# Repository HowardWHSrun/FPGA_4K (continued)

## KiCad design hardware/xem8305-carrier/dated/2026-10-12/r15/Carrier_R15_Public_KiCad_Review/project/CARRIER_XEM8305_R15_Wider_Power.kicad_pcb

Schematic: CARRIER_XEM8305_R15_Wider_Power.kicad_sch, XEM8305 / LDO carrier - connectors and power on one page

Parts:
C5: 220 uF / 25 V; EEE_FK1E221P; MPN EEE-FK1E221P
C6, C38, C48: 0.1 uF / 25 V; C_0402; MPN TMK105BJ104KV-F
C34, C53: 0.1 uF / 10 V; C_0402; MPN C0402C104K8PACTU
C47: 22 uF / 35 V; C_1206; MPN C3216X5R1V226M160AC
C49, C50: 22 uF / 10 V; C_1206; MPN LMK316AB7226KL-TR
C54: 10 pF / 50 V; C_0402; MPN CBR04C100J5GAC
C55: 3.3 nF / 50 V; C_0402; MPN C0402C332K5RACTU
C56: 1 uF / 10 V; C_0402; MPN LMK105BJ105KV-F
C500, C501, C505, C511, C513: 4.7uF; C_0402_1005Metric; MPN JMK105BBJ475MV-F
C502, C503, C504, C506, C507, C508, C509, C512, C514, C515, C516, C517, C518, C519, C520, C522, C525, C526, C527, C528: 100nF; C_0402_1005Metric; MPN C0402C104K8PACTU
C510, C521: 10nF; C_0402_1005Metric; MPN C0402C103K4RACTU
C523, C524: 18pF; C_0402_1005Metric; MPN C0402C180J5GACTU
D4: SMBJ15CA-13-F; D_SMB; MPN SMBJ15CA-13-F
D500: D5V0FS4U10LP-7; Diodes_UDFN-10_1x2.5mm_P0.5mm; MPN D5V0FS4U10LP-7
FB500, FB501, FB502: 600R @100MHz; L_0603_1608Metric; MPN MI0603J601R-10
FB503: 220R @100MHz; L_0805_2012Metric; MPN BLM21PG221SN1D
J1: DF40C(2.0)-50DS-0.4V(51); Hirose_DF40C(2.0)-50DS-0.4V_2x25_P0.4mm; MPN DF40C(2.0)-50DS-0.4V(51)
J4: PJ-102AH; PJ102AH; MPN PJ-102AH
J19: DF40C(2.0)-24DS-0.4V(51); Hirose_DF40C(2.0)-24DS-0.4V_2x12_P0.4mm; MPN DF40C(2.0)-24DS-0.4V(51)
J500: USB4110-GF-A; USB_C_Receptacle_GCT_USB4110; MPN USB4110-GF-A
JP1: REMOVE FOR EXT 3V3; PinHeader_1x02_P2_54; MPN TBD - 2-pin 2.54 mm vertical header plu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
L14: 3.3 uH; Murata_1267AY; MPN 1267AY-3R3N=P3
MC1: ERF6-50-03.5-L-DV-A-K-TR; MPN ERF6-50-03.5-L-DV-A-K-TR
MC2, MC3: ERF6-40-03.5-L-DV-A-K-TR; MPN ERF6-40-03.5-L-DV-A-K-TR
MH1, MH2, MH3, MH4: M3 isolated; MountingHole_3.2mm_M3_Isolated
R75: 10.0 k / 1%; R_0402; MPN CRCW040210K0FKED
R77: 73.2 k / 1%; R_0402; MPN CRCW040273K2FKED
R78: 22.1 k / 1%; R_0402; MPN CRCW040222K1FKEDC
R500, R501: 5.1k; R_0402_1005Metric; MPN CRCW04025K10FKEDC
R502: 12k; R_0402_1005Metric; MPN CRCW040212K0FKED
R503, R510: 10k; R_0402_1005Metric; MPN CRCW040210K0FKED
R507, R508: 100k; R_0402_1005Metric; MPN CRCW0402100KFKED
R509: 2k; R_0402_1005Metric; MPN CRCW04022K00FKED
TP19: 3V3 TEST / EXT+; TestPoint_PTH_D1_Pad2_5
TP20: GND / EXT-; TestPoint_PTH_D1_Pad2_5
U10: TPS54429E; TPS54429E_RSA; MPN TPS54429ERSAR
U500, U502, U503, U504: SN74AXC1T45DBVR; SOT-23-6; MPN SN74AXC1T45DBVR
U501: FT232HQ; QFN-48-1EP_8x8mm_P0.5mm_EP6.2x6.2mm; MPN FT232HQ
U505: 93LC56B-E/MS; MSOP-8_3x3mm_P0.65mm; MPN 93LC56B-E/MS
Y500: 12MHz / 18pF; Crystal_SMD_3225-4Pin_3.2x2.5mm; MPN ABM8-12.000MHZ-B2-T

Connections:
/CHIP_RESET: J1.14 (CHIP_RESET), MC1.85 (B64_L7N)
/CLK32MHZ: J1.36 (CLK32MHZ), MC1.67 (B64_L11P_GC)
/CLKH: J1.12 (CLKH), MC1.78 (B64_L3N)
/D1: J1.4 (D1), MC1.86 (B64_L1N)
/D2: J1.6 (D2), MC1.84 (B64_L1P)
/D3: J1.8 (D3), MC1.82 (B64_L2N)
/D4: J1.10 (D4), MC1.80 (B64_L2P)
/D5: J1.38 (D5), MC1.70 (B64_L5N)
/D6: J1.40 (D6), MC1.68 (B64_L5P)
/D7: J1.42 (D7), MC1.71 (B64_L10P)
/D8: J1.44 (D8), MC1.69 (B64_L11N_GC)
/FE_RESET: J1.20 (FE_RESET), MC1.83 (B64_L7P)
/IMP_TEST: J1.18 (IMP_TEST), MC1.76 (B64_L3P)
/READ: J1.46 (READ), MC1.65 (B64_L12N_GC)
/SPI_CLK: J1.22 (SPI_CLK), MC1.74 (B64_L4N)
/SPI_DINL: J1.26 (SPI_DINL), MC1.79 (B64_L8P)
/SPI_DINR: J1.28 (SPI_DINR), MC1.72 (B64_L4P)
/SPI_LATCH: J1.24 (SPI_LATCH), MC1.81 (B64_L8N)
/STIM_CHB: J1.33 (STIM_CHB), MC1.64 (B64_L6P)
/STIM_CLK: J1.29 (STIM_CLK), MC1.73 (B64_L10N)
/STIM_EN: J1.31 (STIM_EN), MC1.66 (B64_L6N)
/STIM_START: J1.27 (STIM_START), MC1.75 (B64_L9P)
/SYNC: J1.34 (SYNC), MC1.77 (B64_L9N)
/VBST: C53.1, U10.12 (VBST)
BUCK_3V3: C49.2, C50.2, C54.2, JP1.1 (A), L14.2, R77.2, U10.16 (VO)
DGND: C5.2, C6.1, C34.1, C38.1, C47.1, C48.1, C49.1, C50.1, C55.1, C56.1, C500.1, C501.1, C502.1, C503.1, C504.1, C505.1, C506.1, C507.1, C508.1, C509.1, C510.1, C511.1, C512.1, C513.1, C514.1, C515.1, C516.1, C517.1, C518.1, C519.1, C520.1, C521.1, C522.1, C523.1, C524.1, C525.1, C526.1, C527.1, C528.1, D4.1 (A1), D500.3 (A_3), D500.8 (A_8), FB503.2, J1.49 (DGND), J1.50 (DGND), J4.2, J500.A1 (GND_A1), J500.A12 (GND_A12), J500.B1 (GND_B1), J500.B12 (GND_B12), MC1.5 (DGND), MC1.6 (DGND), MC1.7 (DGND), MC1.8 (DGND), MC1.33 (DGND), MC1.34 (DGND), MC1.61 (DGND), MC1.62 (DGND), MC1.92 (DGND), MC1.94 (DGND), MC1.96 (DGND), MC1.98 (DGND), MC1.100 (DGND), MC2.6 (DGND), MC2.9 (DGND), MC2.20 (DGND), MC2.35 (DGND), MC2.45 (DGND), MC2.46 (DGND), MC2.47 (DGND), MC2.72 (DGND), MC2.73 (DGND), MC2.74 (DGND), MC2.76 (DGND), MC3.1 (DGND), MC3.2 (DGND), MC3.7 (DGND), MC3.8 (DGND), MC3.13 (DGND), MC3.14 (DGND), MC3.19 (DGND), MC3.20 (DGND), MC3.25 (DGND), MC3.26 (DGND), MC3.31 (DGND), MC3.32 (DGND), MC3.37 (DGND), MC3.38 (DGND), MC3.43 (DGND), MC3.44 (DGND), MC3.49 (DGND), MC3.50 (DGND), MC3.55 (DGND), MC3.56 (DGND), MC3.61 (DGND), MC3.62 (DGND), MC3.67 (DGND), MC3.68 (DGND), MC3.73 (DGND), MC3.74 (DGND), MC3.79 (DGND), MC3.80 (DGND), R78.1, R500.1, R501.2, R502.1, R508.1, TP20.1, U10.4 (GND), U10.7 (PGND1), U10.8 (PGND2), U10.17 (EP/PGND), U500.2 (GND_2), U501.4 (AGND_4), U501.9 (AGND_9), U501.10 (GND_10), U501.11 (GND_11), U501.22 (GND_22), U501.23 (GND_23), U501.35 (GND_35), U501.36 (GND_36), U501.41 (AGND_41), U501.42 (TEST_42), U501.47 (GND_47), U501.48 (GND_48), U501.49 (EP), U502.2 (GND_2), U503.2 (GND_2), U503.5 (DIR_5), U504.2 (GND_2), U505.5 (VSS_5), Y500.2 (CASE_2), Y500.4 (CASE_4)
GNDADC: MC2.14 (VREFP), MC2.16 (GNDADC)
JTAG_TCK: MC2.1 (JTAG_TCK), U500.4 (B_4)
JTAG_TDI: MC2.3 (JTAG_TDI), U502.4 (B_4)
JTAG_TDO: MC2.7 (JTAG_TDO), U503.4 (B_4)
JTAG_TMS: MC2.5 (JTAG_TMS), U504.4 (B_4)
LDO_3V3: J1.1 (3V3), J1.2 (3V3), JP1.2 (B), TP19.1
unnamed: R75.1, U10.6 (EN)
unnamed: C55.2, U10.3 (SS)
unnamed: C53.2, L14.1, U10.9 (SW1), U10.10 (SW2), U10.11 (SW3)
unnamed: C54.1, R77.1, R78.2, U10.1 (VFB)
unnamed: C56.2, U10.2 (VREG5)
USBJTAG_3V3: C500.2, C503.2, C507.2, C508.2, C509.2, C513.2, C514.2, C515.2, C519.2, C525.2, C527.2, FB500.1, FB501.1, R503.2, R507.2, R510.2, U500.1 (Vcca_1), U500.5 (DIR_5), U501.12 (VCCIO_12), U501.24 (VCCIO_24), U501.39 (VCCD_39), U501.46 (VCCIO_46), U502.1 (Vcca_1), U502.5 (DIR_5), U503.1 (Vcca_1), U504.1 (Vcca_1), U504.5 (DIR_5), U505.8 (VCC_8)
USBJTAG_CC1: J500.A5 (CC1_A5), R500.2
USBJTAG_CC2: J500.B5 (CC2_B5), R501.1
USBJTAG_EECLK: R507.1, U501.44 (EECLK_44), U505.2 (CLK_2)
USBJTAG_EECS: R508.2, U501.45 (EECS_45), U505.1 (CS_1)
USBJTAG_EEDATA: R509.1, U501.43 (EEDATA_43), U505.3 (DI_3)
USBJTAG_EEPROM_DO: R509.2, R510.1, U505.4 (DO_4)
USBJTAG_ESD_UNUSED: D500.1 (K_1), D500.10 (K_10)
USBJTAG_FT232_RESET: C521.2, R503.1, U501.34 (~RESET_34)
USBJTAG_FTDI_TCK: U500.3 (A_3), U501.13 (ADBUS0_/_TCK_/_SK_13)
USBJTAG_FTDI_TDI: U501.14 (ADBUS1_/_TDI_/_DO_14), U502.3 (A_3)
USBJTAG_FTDI_TDO: U501.15 (ADBUS2_/_TDO_/_DI_15), U503.3 (A_3)
USBJTAG_FTDI_TMS: U501.16 (ADBUS3_/_TMS_/_CS_16), U504.3 (A_3)
USBJTAG_OSCI: C523.2, U501.1 (OSCI_1), Y500.1 (OSC1_1)
USBJTAG_OSCO: C524.2, U501.2 (OSCO_2), Y500.3 (OSC2_3)
USBJTAG_REF: R502.2, U501.5 (REF_5)
USBJTAG_SHIELD: C522.2, FB503.1, J500.SH (SHELL_M4)
USBJTAG_USB_DN: D500.5 (K_5), D500.6 (K_6), J500.A7 (DN1_A7), J500.B7 (DN2_B7), U501.6 (DM_6)
USBJTAG_USB_DP: D500.4 (K_4), D500.7 (K_7), J500.A6 (DP1_A6), J500.B6 (DP2_B6), U501.7 (DP_7)
USBJTAG_VBUS_C: C510.2, D500.2 (K_2), D500.9 (K_9), FB502.2, J500.A4 (VBUS_A4), J500.A9 (VBUS_A9), J500.B4 (VBUS_B4), J500.B9 (VBUS_B9)
USBJTAG_VCCA: C518.2, U501.37 (VCCA_37)
USBJTAG_VCORE: C517.2, U501.38 (VCORE_38)
USBJTAG_VPHY: C505.2, C506.2, FB501.2, U501.3 (VPHY_3)
USBJTAG_VPLL: C501.2, C502.2, FB500.2, U501.8 (VPLL_8)
USBJTAG_VREGIN: C511.2, C512.2, FB502.1, U501.40 (VREGIN_40)
VDCIN: C5.1, C6.2, C38.2, C47.2, C48.2, D4.2 (A2), J4.1, MC1.91 (VDCIN), MC1.93 (VDCIN), MC1.95 (VDCIN), MC1.97 (VDCIN), MC1.99 (VDCIN), R75.2, U10.13 (VIN1), U10.14 (VIN2), U10.15 (VIN3)
XEM_1V8: C34.2, C504.2, C516.2, C520.2, C526.2, C528.2, MC1.1 (VCCO_84), MC1.2 (VCCO_64), MC1.3 (VCCO_84), MC1.4 (VCCO_64), MC2.37 (VCCO_85), MC2.39 (VCCO_85), MC2.41 (VCCO_86), MC2.43 (VCCO_86), MC2.75 (1V8_OUT), MC2.77 (1V8_OUT), MC2.79 (1V8_OUT), U500.6 (Vccb_6), U502.6 (Vccb_6), U503.6 (Vccb_6), U504.6 (Vccb_6)

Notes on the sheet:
4 FPGA BANK POWER - BRK8305 A03
XEM exports 1.8 V at MC2 pins 75 / 77 / 79. No additional regulator.
POWER FLOW
Input TVS
3 TEST / EXTERNAL 3.3 V INPUT
C47 / C48: input bypass. L14 + C49 / C50: output filter. R77 / R78 + C54: feedback.
C53: bootstrap. C55: soft start. C56: bias bypass. R75: always-on enable; XEM_PG link omitted.
12 V -> BRK converter -> JP1 -> LDO J1 pins 1 / 2
XEM 1.8 V directly feeds all four FPGA banks; ASIC supplies stay on the LDO board.
CONNECTORS - preserved foundation pin map
LDO assembly revision / ground return and hardware operation remain review items.
External regulated 12 V - selected for BRK converter. Center positive.
2 3.3 V SUPPLY FOR THE EXISTING LDO BOARD
Bank64 carries our ASIC signals. FPGA I/O setting: LVCMOS18.
U10 / L14 make BUCK_3V3; JP1 connects it to LDO_3V3.
VDCIN powers the XEM through MC1.
MC1 local bypass
1 MAIN INPUT - BRK8305 A03
VREFP directly connects to module GNDADC for internal reference; GNDADC stays separate from DGND.
MC1 VDCIN: 91 / 93 / 95 / 97 / 99. Native 12 V distribution plane and branch.
Bulk reservoir
12 V enters J4 and becomes VDCIN.
LDO_3V3 feeds LDO J1 pins 1 and 2.
Jack bypass
5 INTERNAL FPGA MONITOR REFERENCE
6 STIMULATION POWER - LDO BOARD RESPONSIBILITY
Howard relays Gerald: supply 3.3 V; the LDO board handles stimulation power.
Carrier boundary: existing LDO_3V3 feed. No extra stimulation converters selected.
Older saved LDO source has separate J15 / J8 inputs; verify the matching revision.
Owner-reported boundary recorded; the older source is not proof of 3.3 V-only operation.
7 USB-C JTAG — FT232H / BRK8305-DERIVED / 1.8 V TARGET
USB VBUS powers bridge only. FTDI 3.3 V is separate from LDO 3.3 V.
Blank EEPROM requires AMD program_ftdi provisioning; validate discovery / IDCODE / ILA.
8 XEM MOUNTING / ISOLATED COPPER RINGS
Four plated holes: 3.2 mm bore / 6.4 mm ring. Electrically isolated.
XEM nominal connector stack: 5.0 mm; choose matching standoffs.
USB shield: BRK fitted C522 + FB503; source DNP shunts remain omitted.

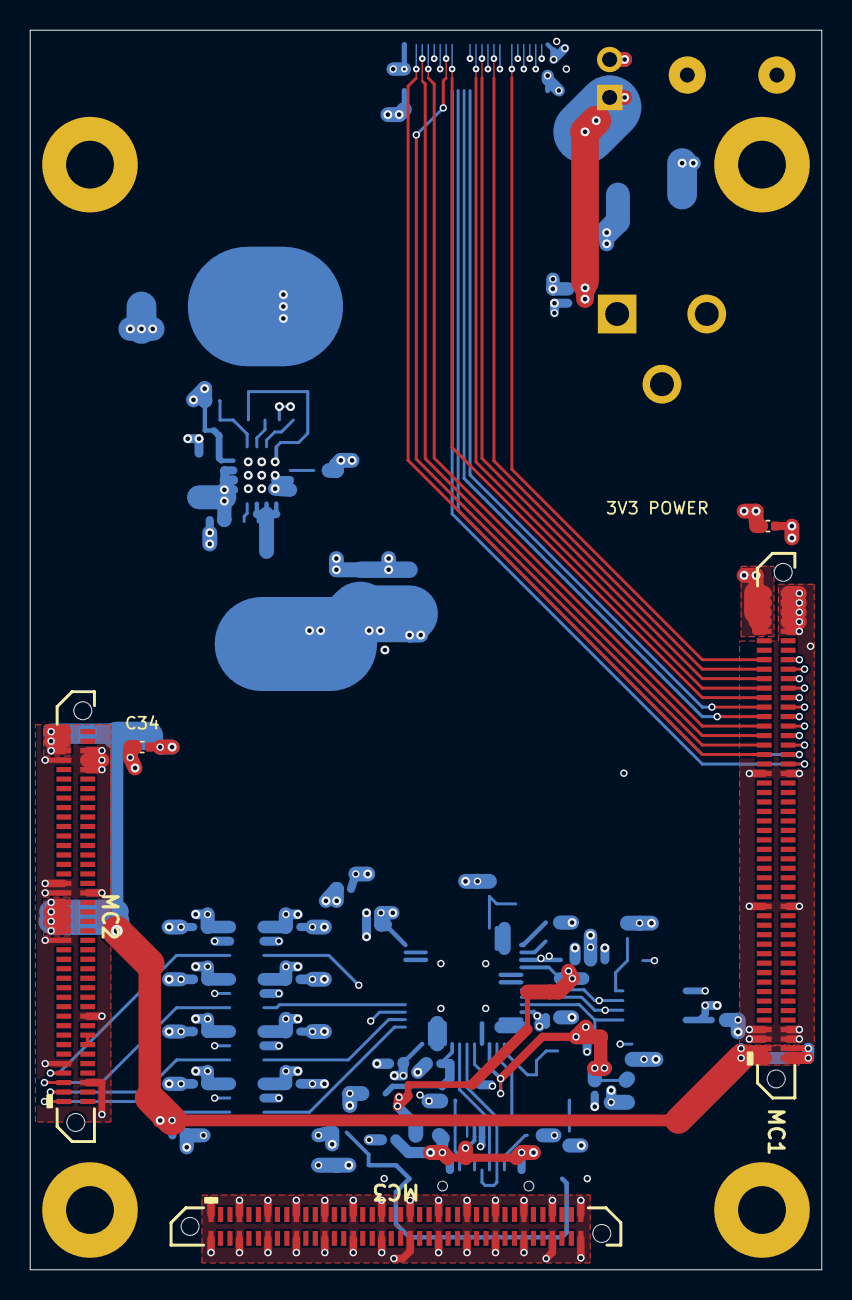
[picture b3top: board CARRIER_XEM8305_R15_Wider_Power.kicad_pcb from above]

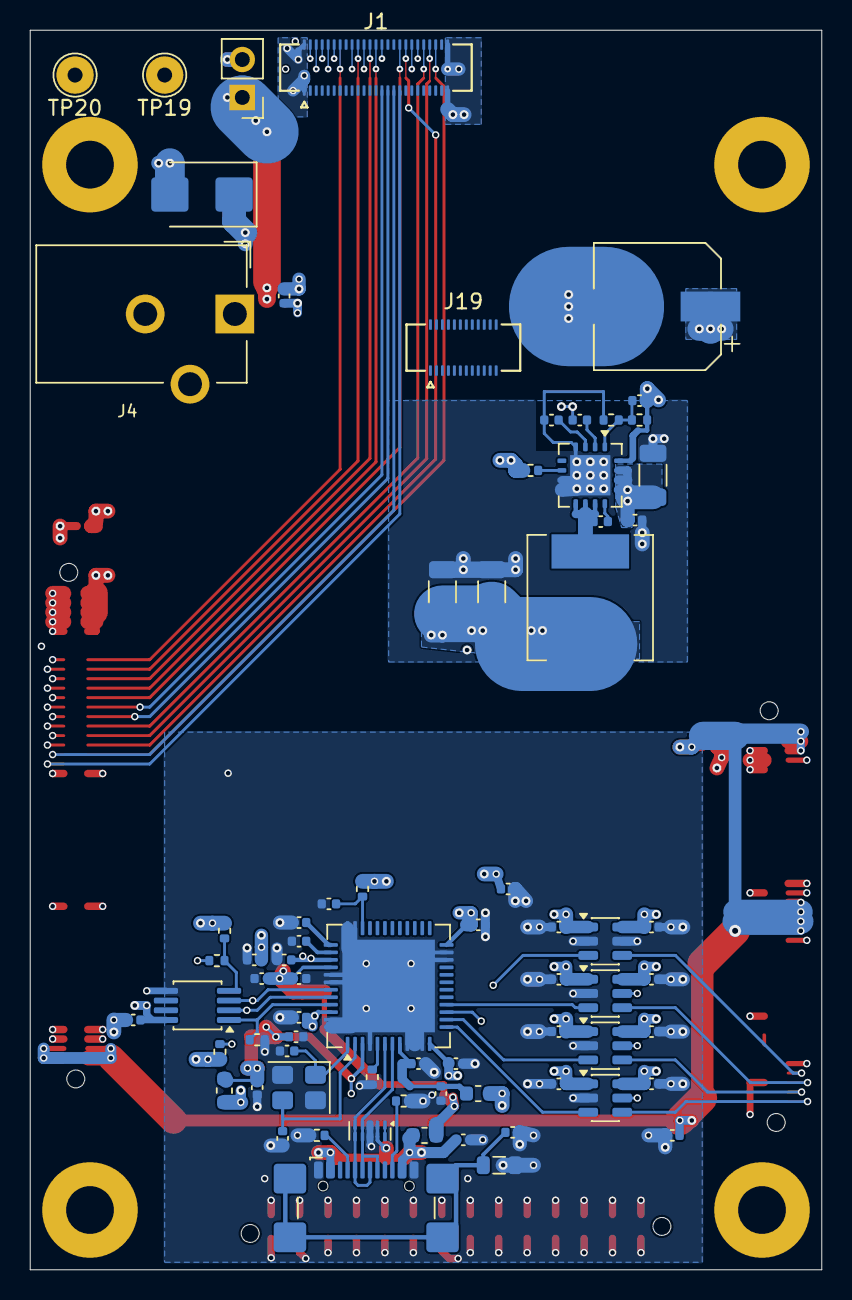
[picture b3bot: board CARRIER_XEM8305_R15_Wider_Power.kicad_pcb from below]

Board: 6 copper layers, 53.0 x 83.0 mm, 81 parts (72 on the bottom side), 64 nets.

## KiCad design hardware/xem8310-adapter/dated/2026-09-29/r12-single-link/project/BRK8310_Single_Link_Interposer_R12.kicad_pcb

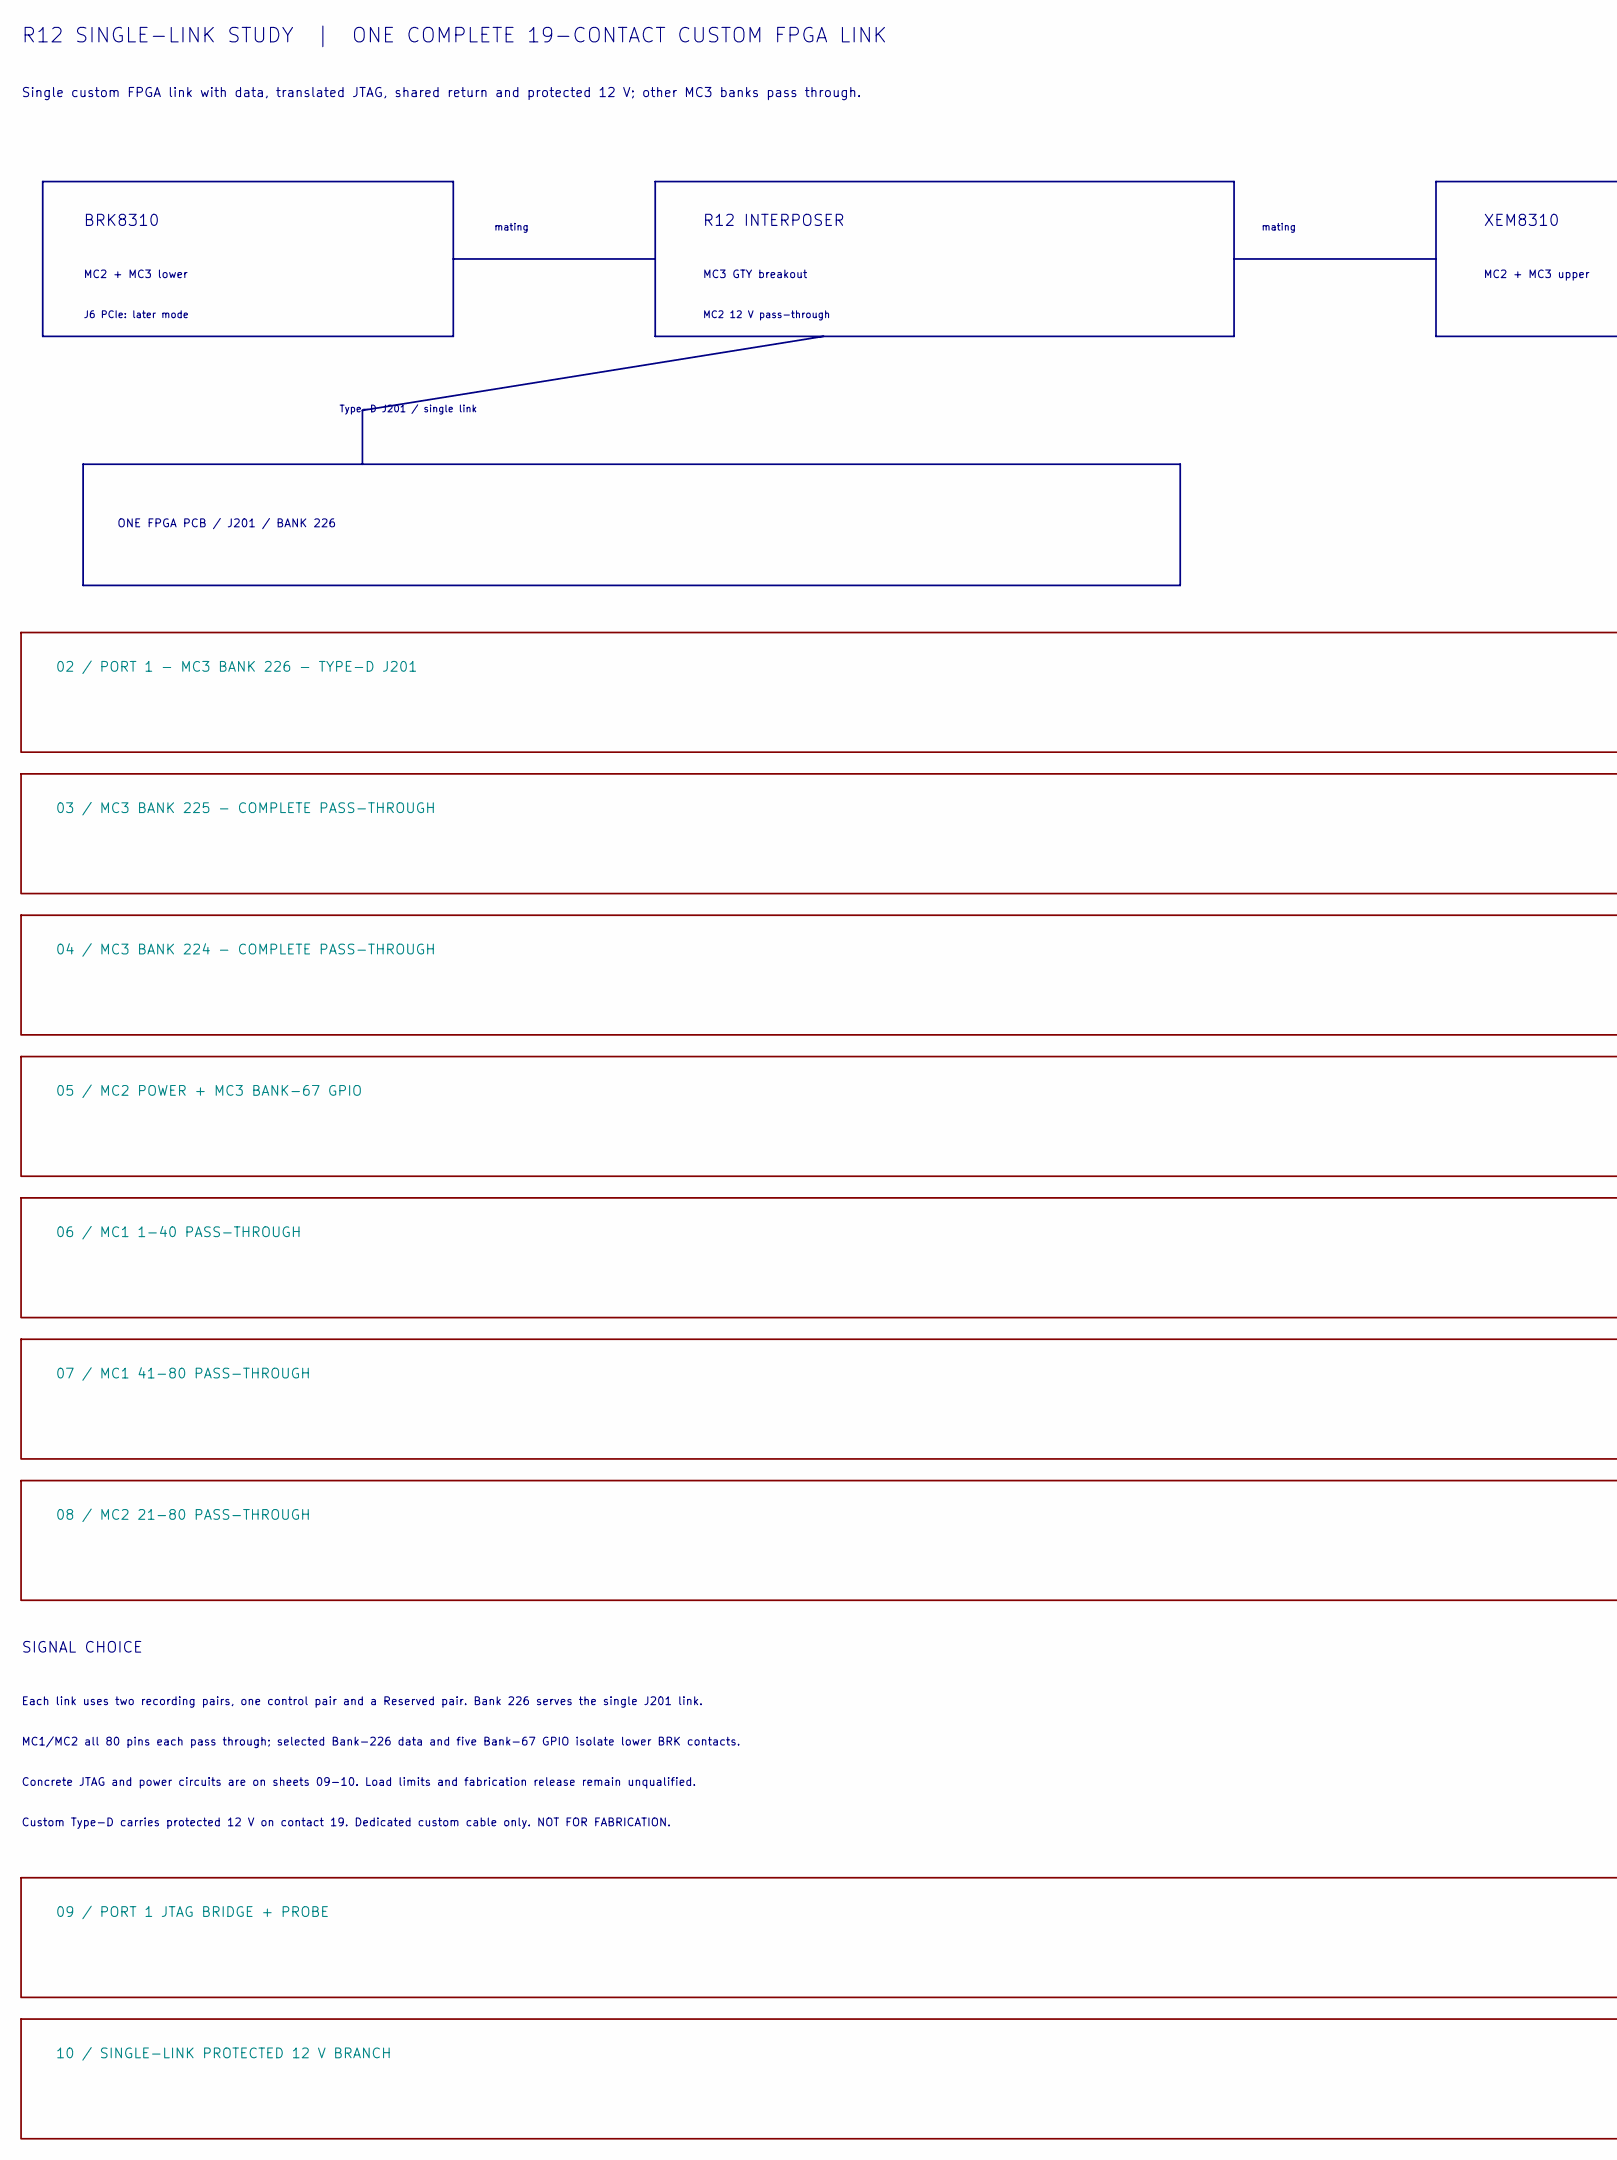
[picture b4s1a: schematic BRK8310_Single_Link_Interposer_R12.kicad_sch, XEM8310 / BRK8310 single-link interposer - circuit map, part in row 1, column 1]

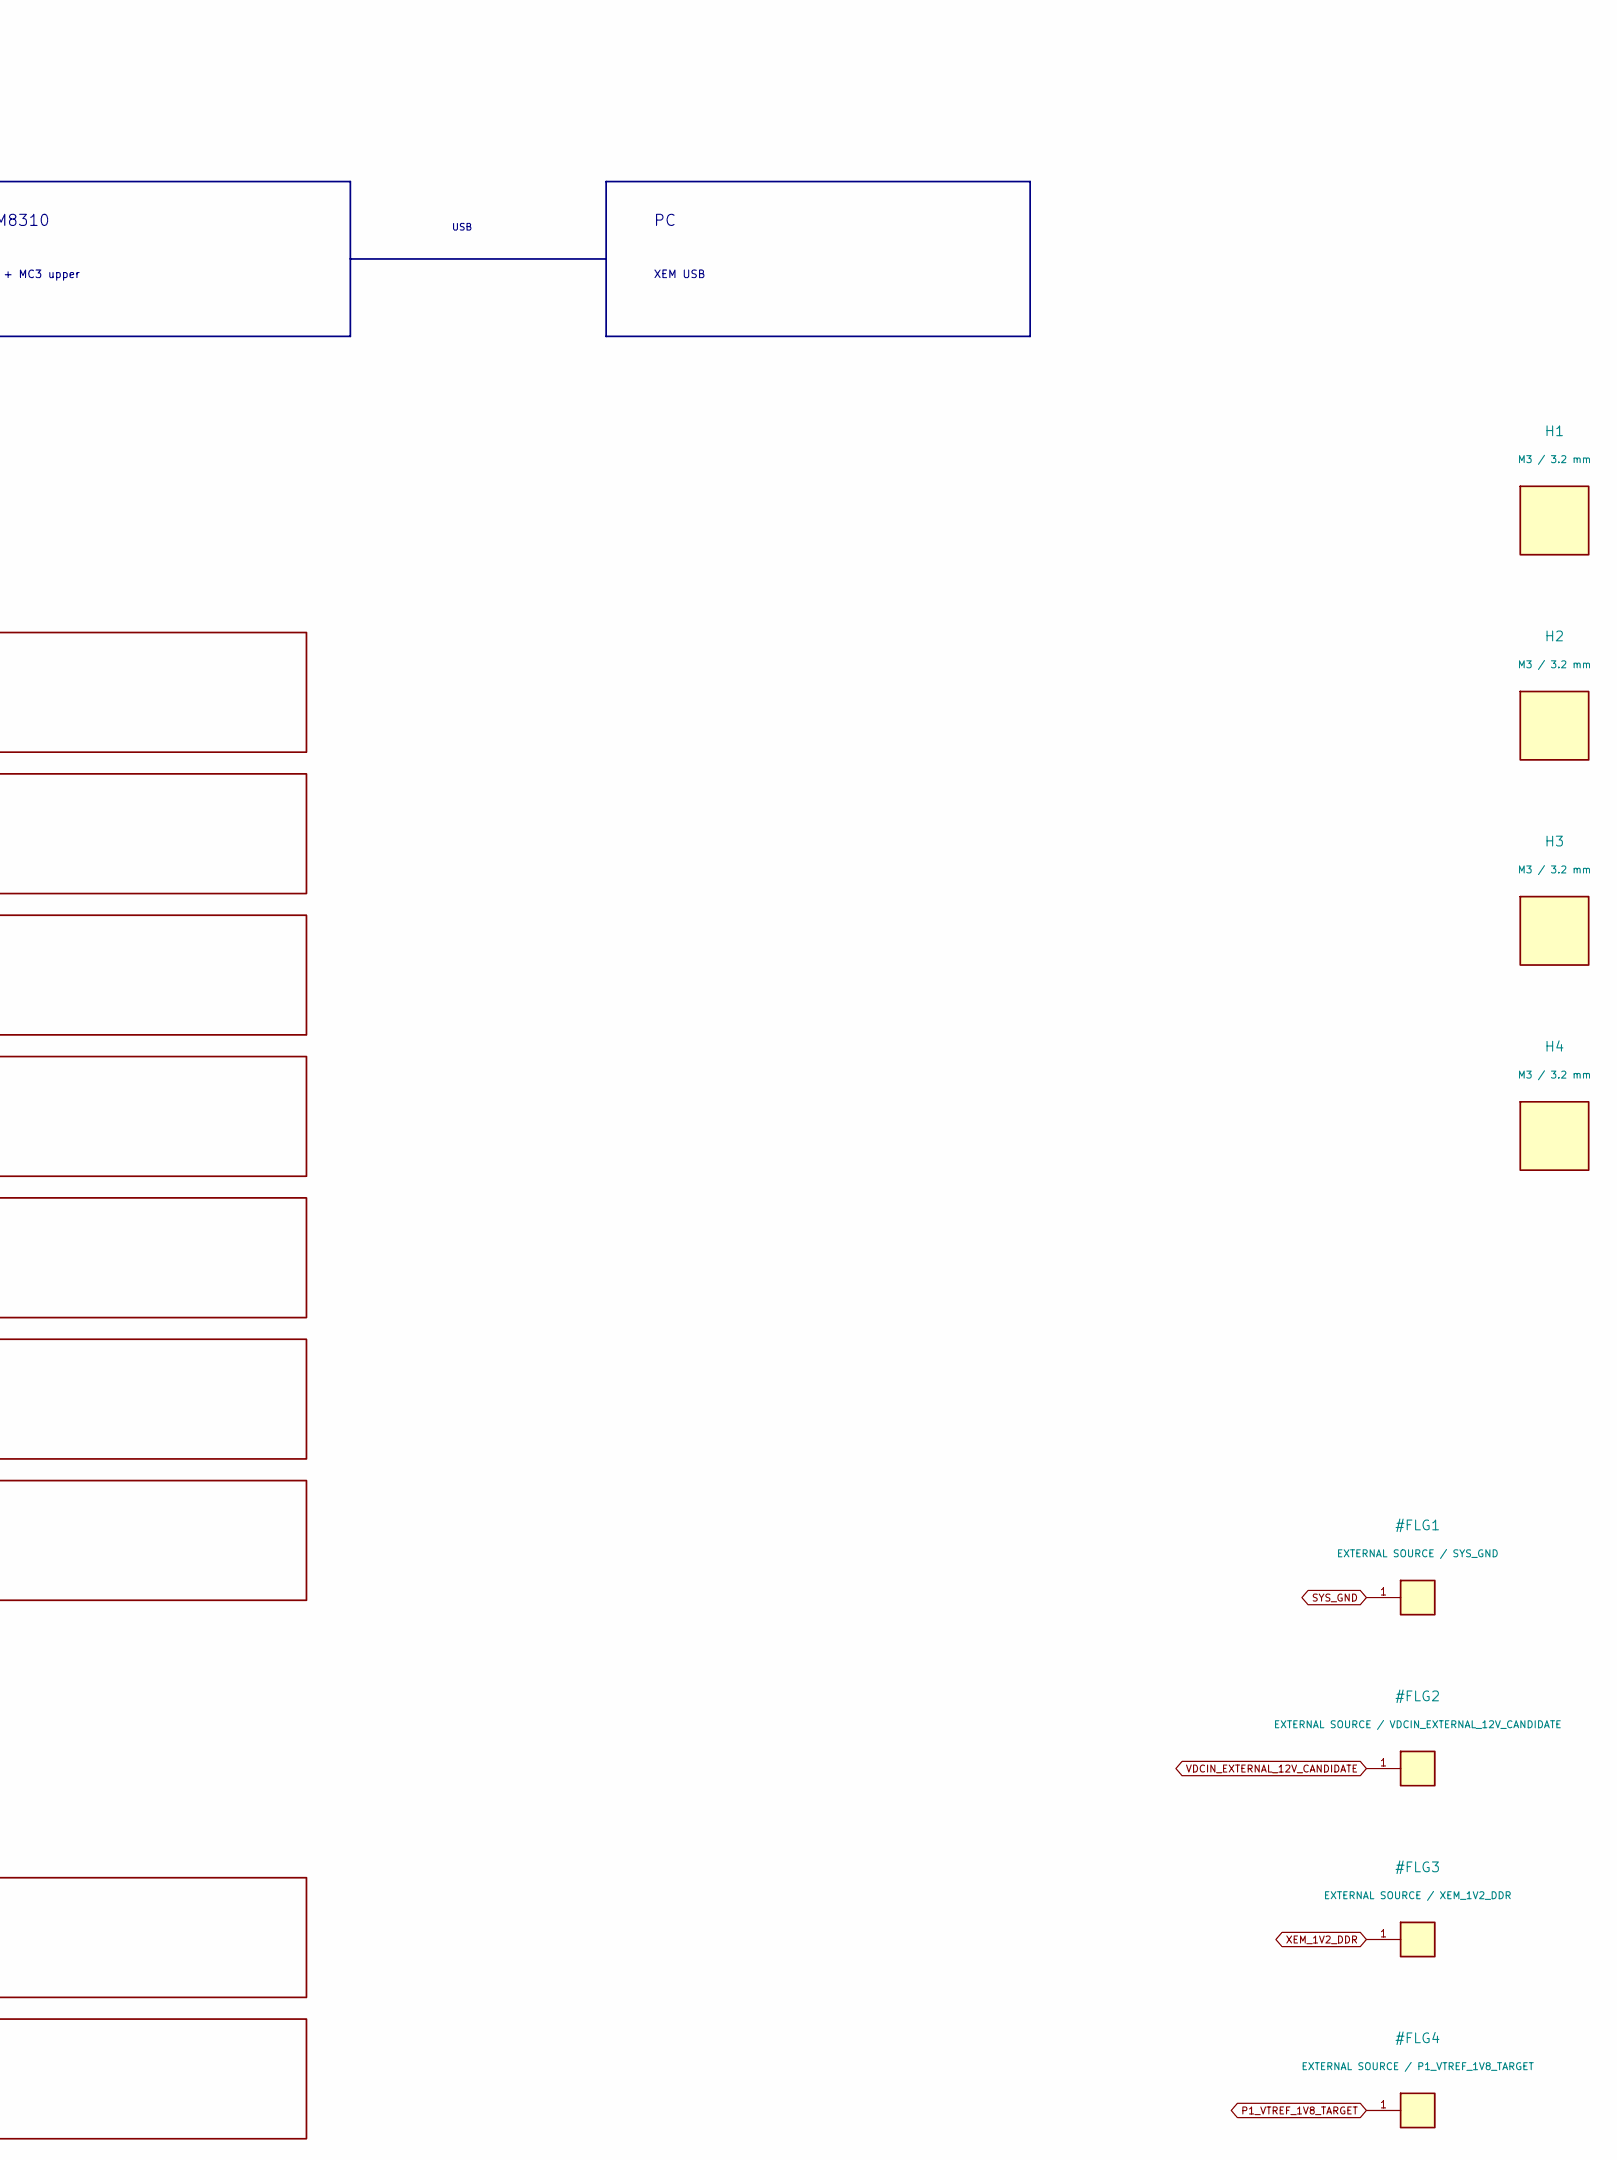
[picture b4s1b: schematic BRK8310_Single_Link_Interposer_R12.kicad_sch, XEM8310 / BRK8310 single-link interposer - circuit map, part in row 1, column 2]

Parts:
H1, H2, H3, H4: M3 / 3.2 mm; MountingHole_3.2mm_M3

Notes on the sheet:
R12 SINGLE-LINK STUDY | ONE COMPLETE 19-CONTACT CUSTOM FPGA LINK
Single custom FPGA link with data, translated JTAG, shared return and protected 12 V; other MC3 banks pass through.
BRK8310
MC2 + MC3 lower
J6 PCIe: later mode
R12 INTERPOSER
MC3 GTY breakout
MC2 12 V pass-through
XEM8310
MC2 + MC3 upper
XEM USB
mating
USB
ONE FPGA PCB / J201 / BANK 226
Type-D J201 / single link
SIGNAL CHOICE
Each link uses two recording pairs, one control pair and a Reserved pair. Bank 226 serves the single J201 link.
MC1/MC2 all 80 pins each pass through; selected Bank-226 data and five Bank-67 GPIO isolate lower BRK contacts.
Concrete JTAG and power circuits are on sheets 09-10. Load limits and fabrication release remain unqualified.
Custom Type-D carries protected 12 V on contact 19. Dedicated custom cable only. NOT FOR FABRICATION.

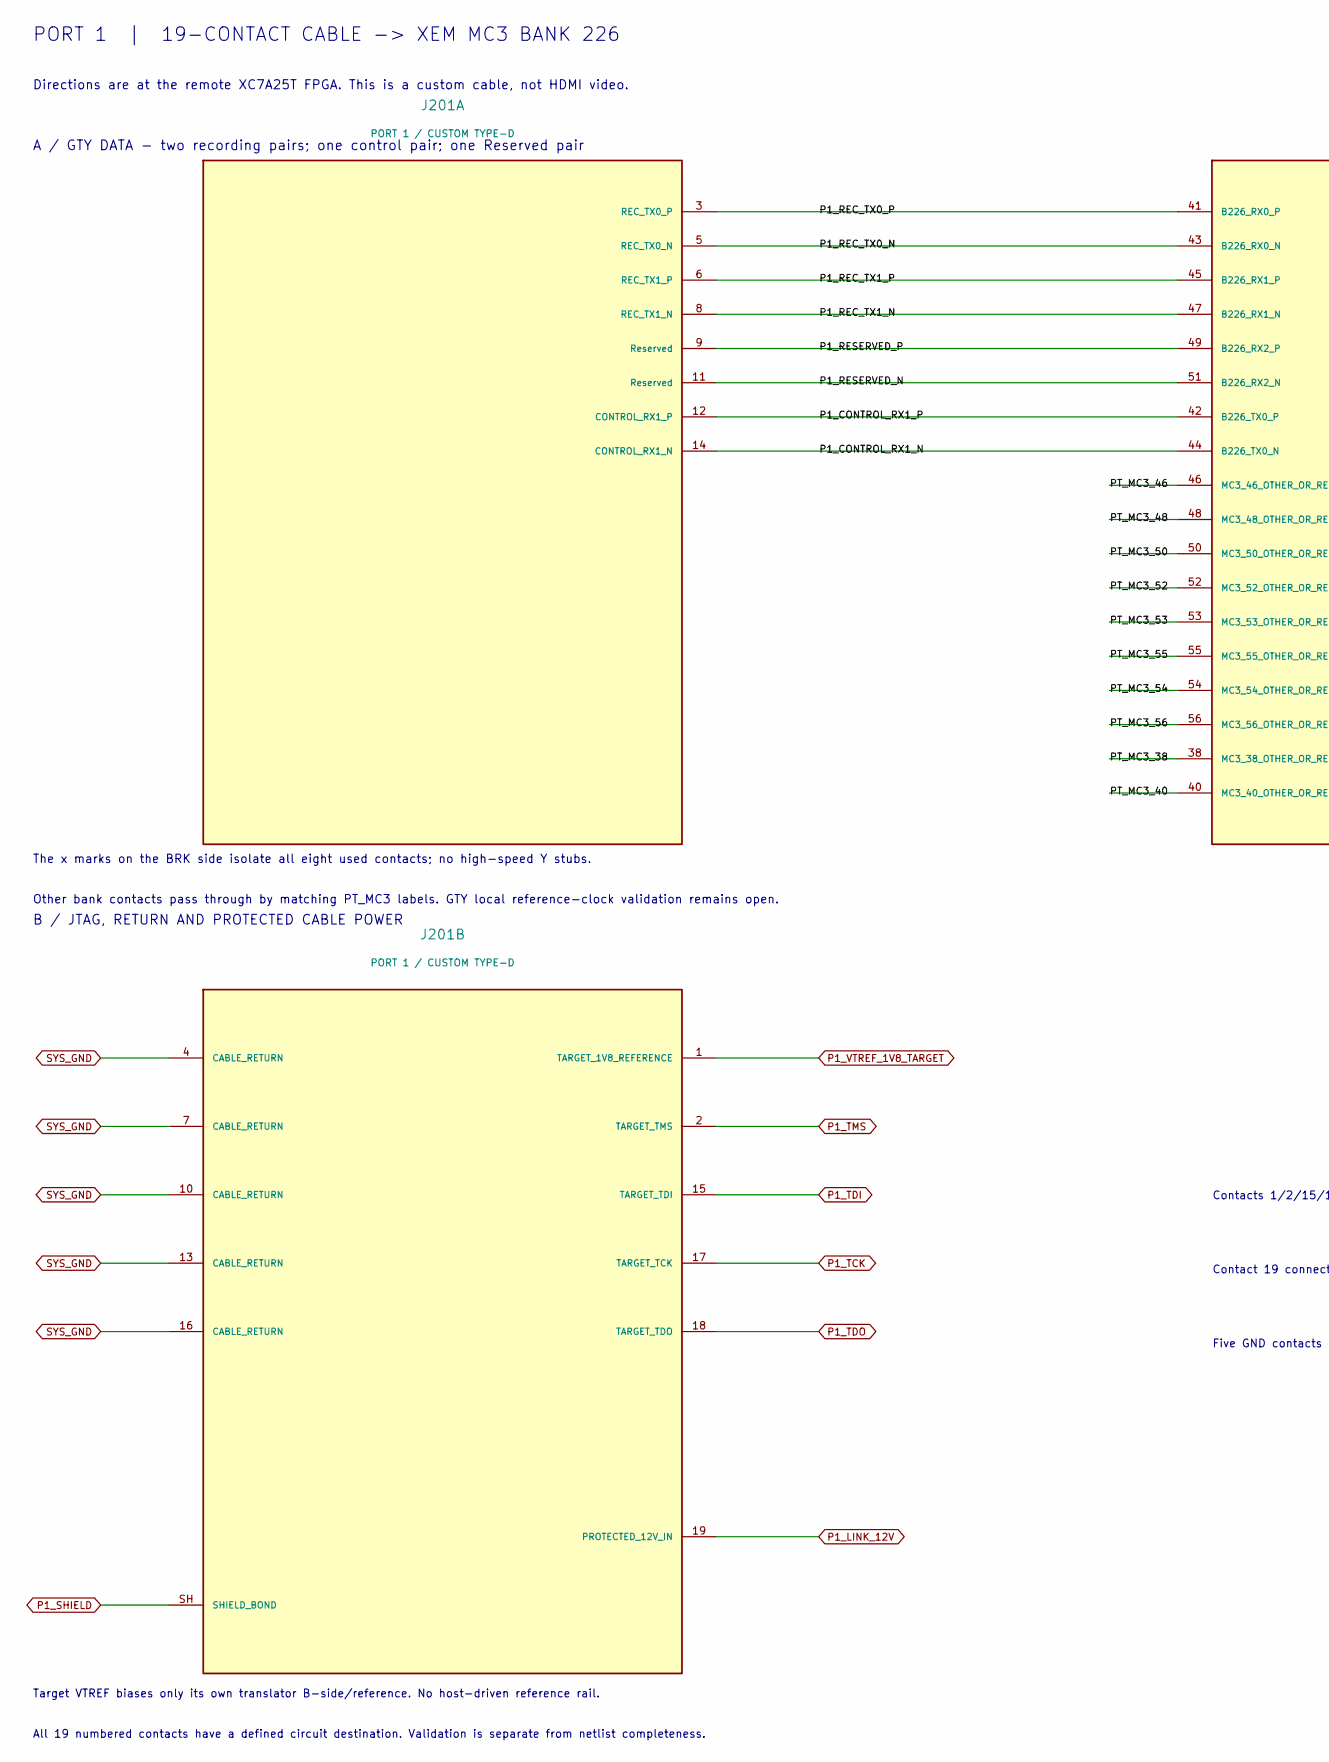
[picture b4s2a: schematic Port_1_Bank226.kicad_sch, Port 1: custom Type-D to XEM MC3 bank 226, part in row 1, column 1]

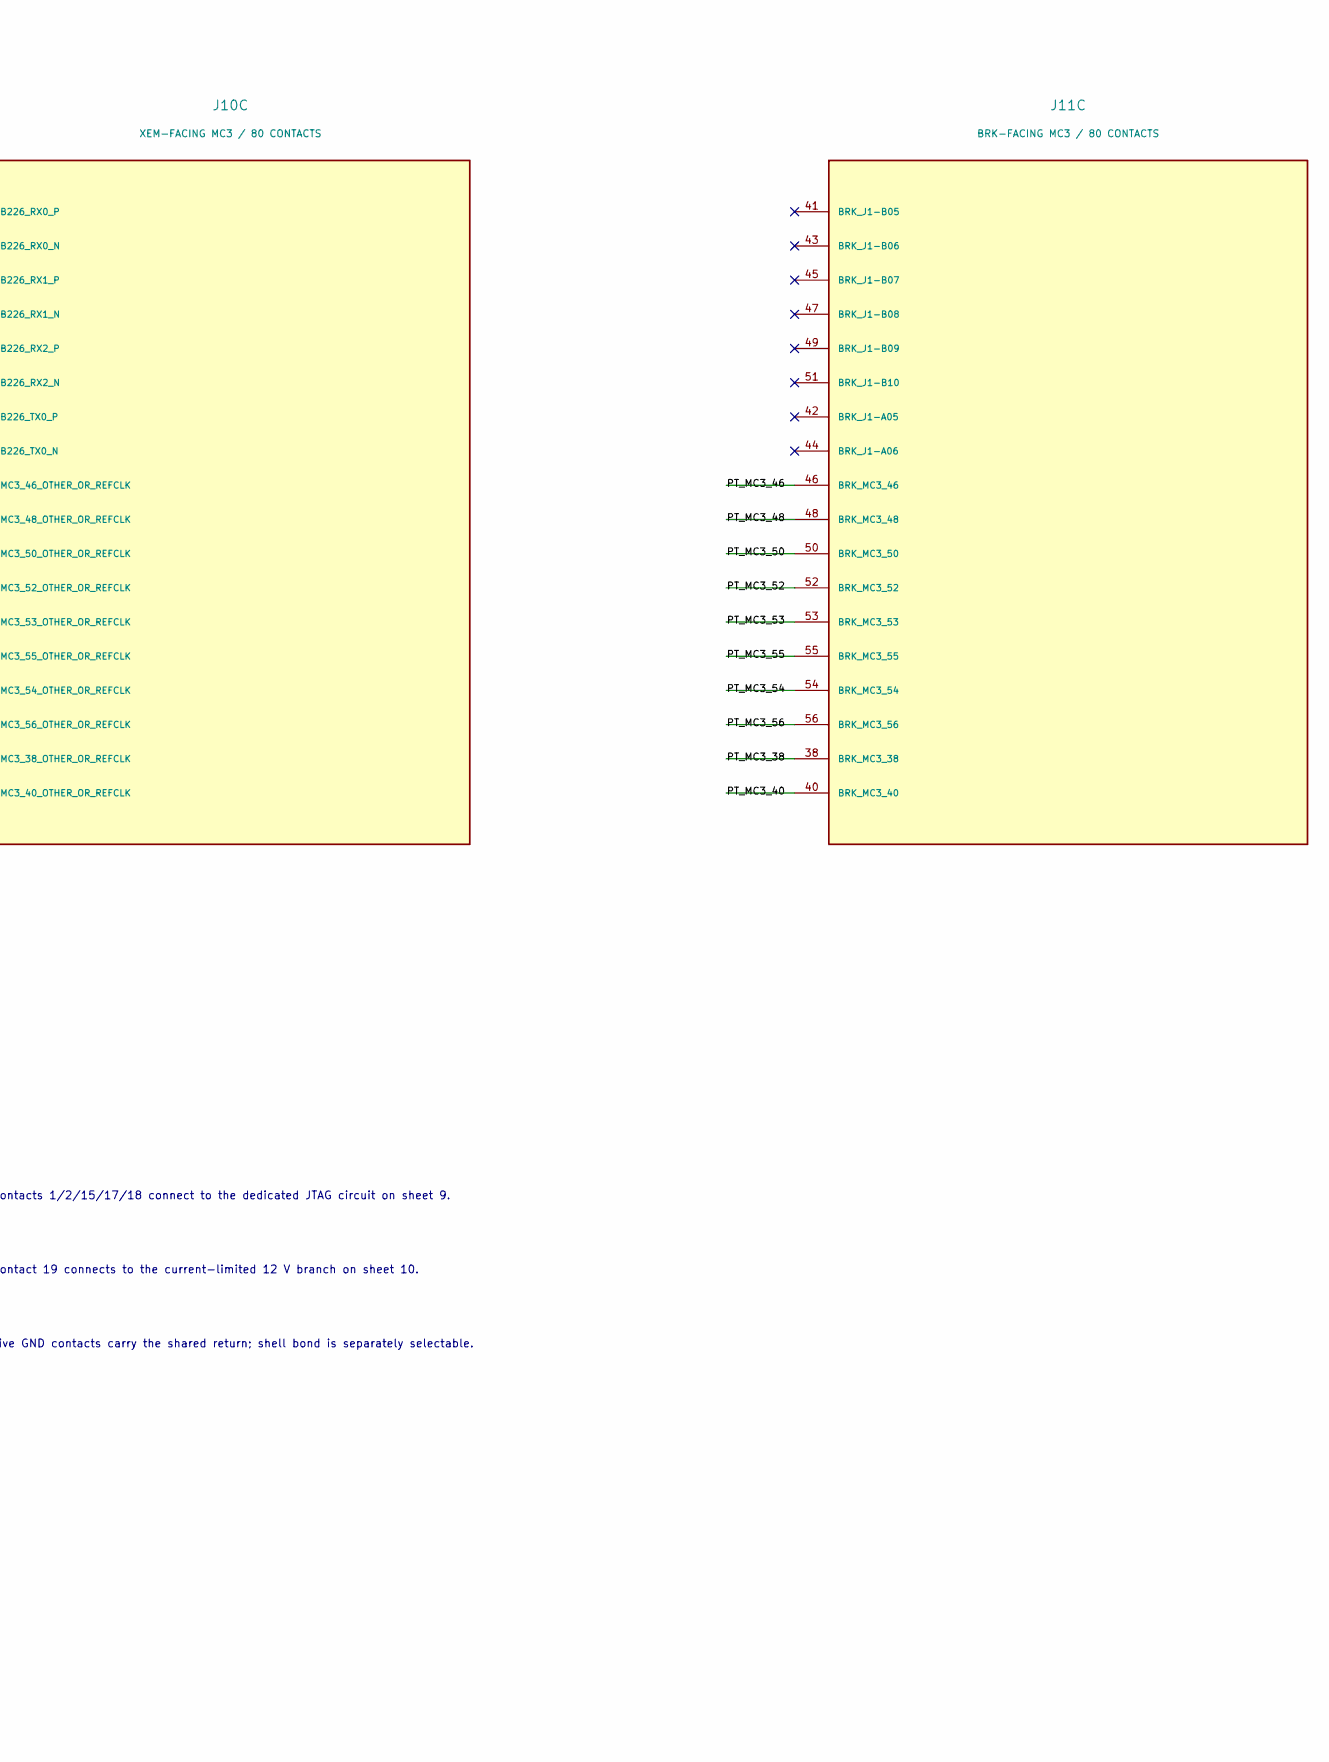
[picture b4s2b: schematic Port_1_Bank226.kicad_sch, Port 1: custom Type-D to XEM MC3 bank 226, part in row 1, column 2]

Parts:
J10: XEM-FACING MC3 / 80 CONTACTS; QTH_040_01_Top_OpalKelly
J11: BRK-FACING MC3 / 80 CONTACTS; QSH_040_01_Bottom_SamtecDrawing
J201: PORT 1 / CUSTOM TYPE-D; HDMI_Micro-D_Molex_46765-1xxx

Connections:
/02 / PORT 1 - MC3 BANK 226 - TYPE-D J201/P1_CONTROL_RX1_N: J10.44 (B226_TX0_N), J201.14 (CONTROL_RX1_N)
/02 / PORT 1 - MC3 BANK 226 - TYPE-D J201/P1_CONTROL_RX1_P: J10.42 (B226_TX0_P), J201.12 (CONTROL_RX1_P)
/02 / PORT 1 - MC3 BANK 226 - TYPE-D J201/P1_REC_TX0_N: J10.43 (B226_RX0_N), J201.5 (REC_TX0_N)
/02 / PORT 1 - MC3 BANK 226 - TYPE-D J201/P1_REC_TX0_P: J10.41 (B226_RX0_P), J201.3 (REC_TX0_P)
/02 / PORT 1 - MC3 BANK 226 - TYPE-D J201/P1_REC_TX1_N: J10.47 (B226_RX1_N), J201.8 (REC_TX1_N)
/02 / PORT 1 - MC3 BANK 226 - TYPE-D J201/P1_REC_TX1_P: J10.45 (B226_RX1_P), J201.6 (REC_TX1_P)
/02 / PORT 1 - MC3 BANK 226 - TYPE-D J201/P1_RESERVED_N: J10.51 (B226_RX2_N), J201.11 (Reserved)
/02 / PORT 1 - MC3 BANK 226 - TYPE-D J201/P1_RESERVED_P: J10.49 (B226_RX2_P), J201.9 (Reserved)
/02 / PORT 1 - MC3 BANK 226 - TYPE-D J201/PT_MC3_38: J10.38 (MC3_38_OTHER_OR_REFCLK), J11.38 (BRK_MC3_38)
/02 / PORT 1 - MC3 BANK 226 - TYPE-D J201/PT_MC3_40: J10.40 (MC3_40_OTHER_OR_REFCLK), J11.40 (BRK_MC3_40)
/02 / PORT 1 - MC3 BANK 226 - TYPE-D J201/PT_MC3_46: J10.46 (MC3_46_OTHER_OR_REFCLK), J11.46 (BRK_MC3_46)
/02 / PORT 1 - MC3 BANK 226 - TYPE-D J201/PT_MC3_48: J10.48 (MC3_48_OTHER_OR_REFCLK), J11.48 (BRK_MC3_48)
/02 / PORT 1 - MC3 BANK 226 - TYPE-D J201/PT_MC3_50: J10.50 (MC3_50_OTHER_OR_REFCLK), J11.50 (BRK_MC3_50)
/02 / PORT 1 - MC3 BANK 226 - TYPE-D J201/PT_MC3_52: J10.52 (MC3_52_OTHER_OR_REFCLK), J11.52 (BRK_MC3_52)
/02 / PORT 1 - MC3 BANK 226 - TYPE-D J201/PT_MC3_53: J10.53 (MC3_53_OTHER_OR_REFCLK), J11.53 (BRK_MC3_53)
/02 / PORT 1 - MC3 BANK 226 - TYPE-D J201/PT_MC3_54: J10.54 (MC3_54_OTHER_OR_REFCLK), J11.54 (BRK_MC3_54)
/02 / PORT 1 - MC3 BANK 226 - TYPE-D J201/PT_MC3_55: J10.55 (MC3_55_OTHER_OR_REFCLK), J11.55 (BRK_MC3_55)
/02 / PORT 1 - MC3 BANK 226 - TYPE-D J201/PT_MC3_56: J10.56 (MC3_56_OTHER_OR_REFCLK), J11.56 (BRK_MC3_56)
P1_LINK_12V: J201.19 (PROTECTED_12V_IN); also elsewhere on the board
P1_SHIELD: J201.SH (SHIELD_BOND); also elsewhere on the board
P1_TCK: J201.17 (TARGET_TCK); also elsewhere on the board
P1_TDI: J201.15 (TARGET_TDI); also elsewhere on the board
P1_TDO: J201.18 (TARGET_TDO); also elsewhere on the board
P1_TMS: J201.2 (TARGET_TMS); also elsewhere on the board
P1_VTREF_1V8_TARGET: J201.1 (TARGET_1V8_REFERENCE); also elsewhere on the board
SYS_GND: J201.4 (CABLE_RETURN), J201.7 (CABLE_RETURN), J201.10 (CABLE_RETURN), J201.13 (CABLE_RETURN), J201.16 (CABLE_RETURN); also elsewhere on the board

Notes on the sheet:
PORT 1 | 19-CONTACT CABLE -> XEM MC3 BANK 226
Directions are at the remote XC7A25T FPGA. This is a custom cable, not HDMI video.
A / GTY DATA - two recording pairs; one control pair; one Reserved pair
The x marks on the BRK side isolate all eight used contacts; no high-speed Y stubs.
Other bank contacts pass through by matching PT_MC3 labels. GTY local reference-clock validation remains open.
B / JTAG, RETURN AND PROTECTED CABLE POWER
Contacts 1/2/15/17/18 connect to the dedicated JTAG circuit on sheet 9.
Contact 19 connects to the current-limited 12 V branch on sheet 10.
Five GND contacts carry the shared return; shell bond is separately selectable.
Target VTREF biases only its own translator B-side/reference. No host-driven reference rail.
All 19 numbered contacts have a defined circuit destination. Validation is separate from netlist completeness.
